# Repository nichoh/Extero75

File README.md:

# Extero75
keyboard

75% keyboard with 10 more extra keys and a knob on the left hand side. Will use USB C and have Backlight LED.

Progress:
Schematic is currently getting checked while doing some routing.

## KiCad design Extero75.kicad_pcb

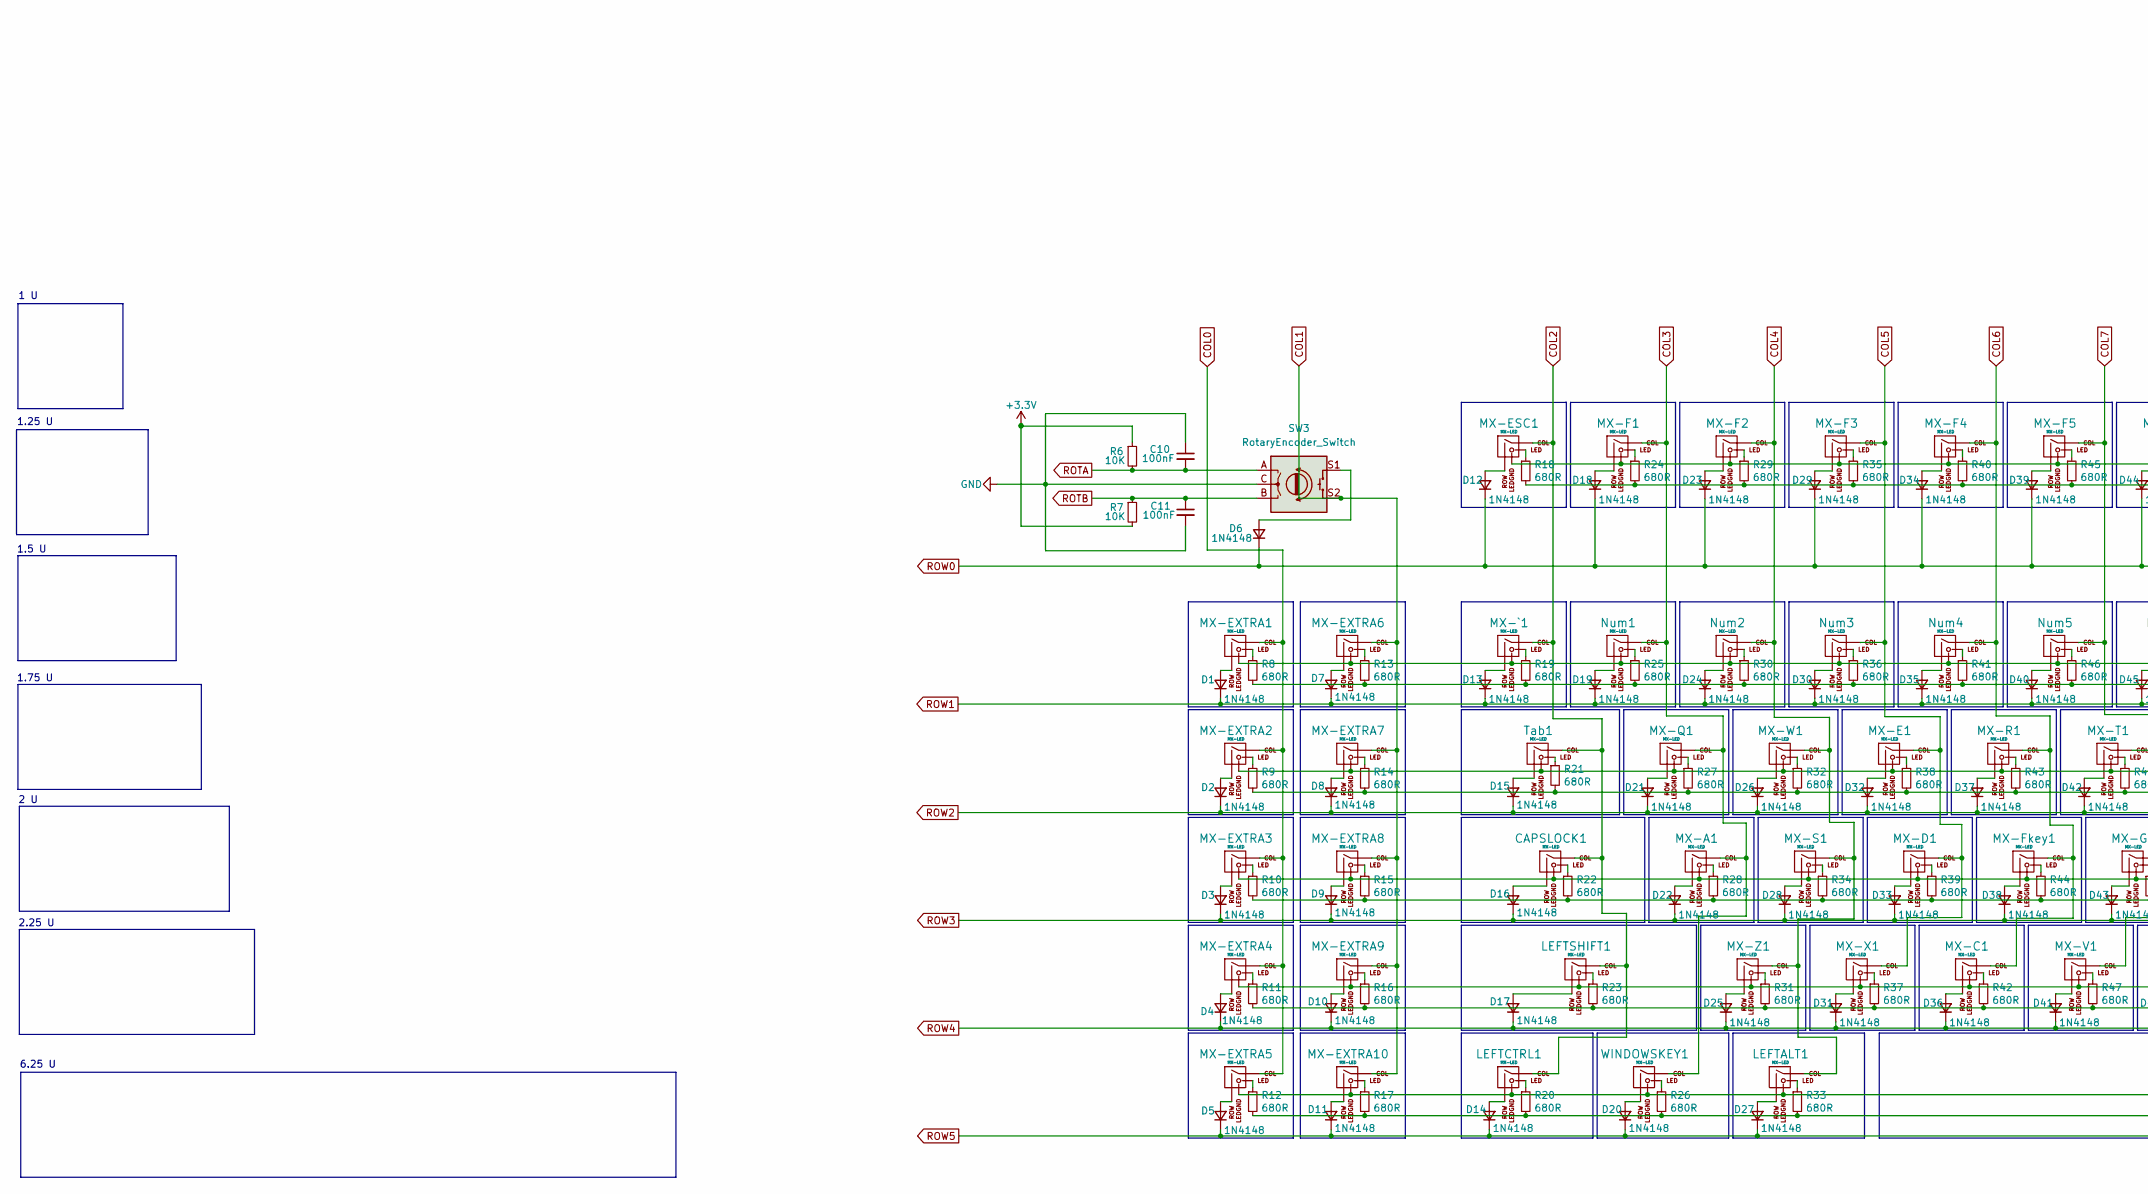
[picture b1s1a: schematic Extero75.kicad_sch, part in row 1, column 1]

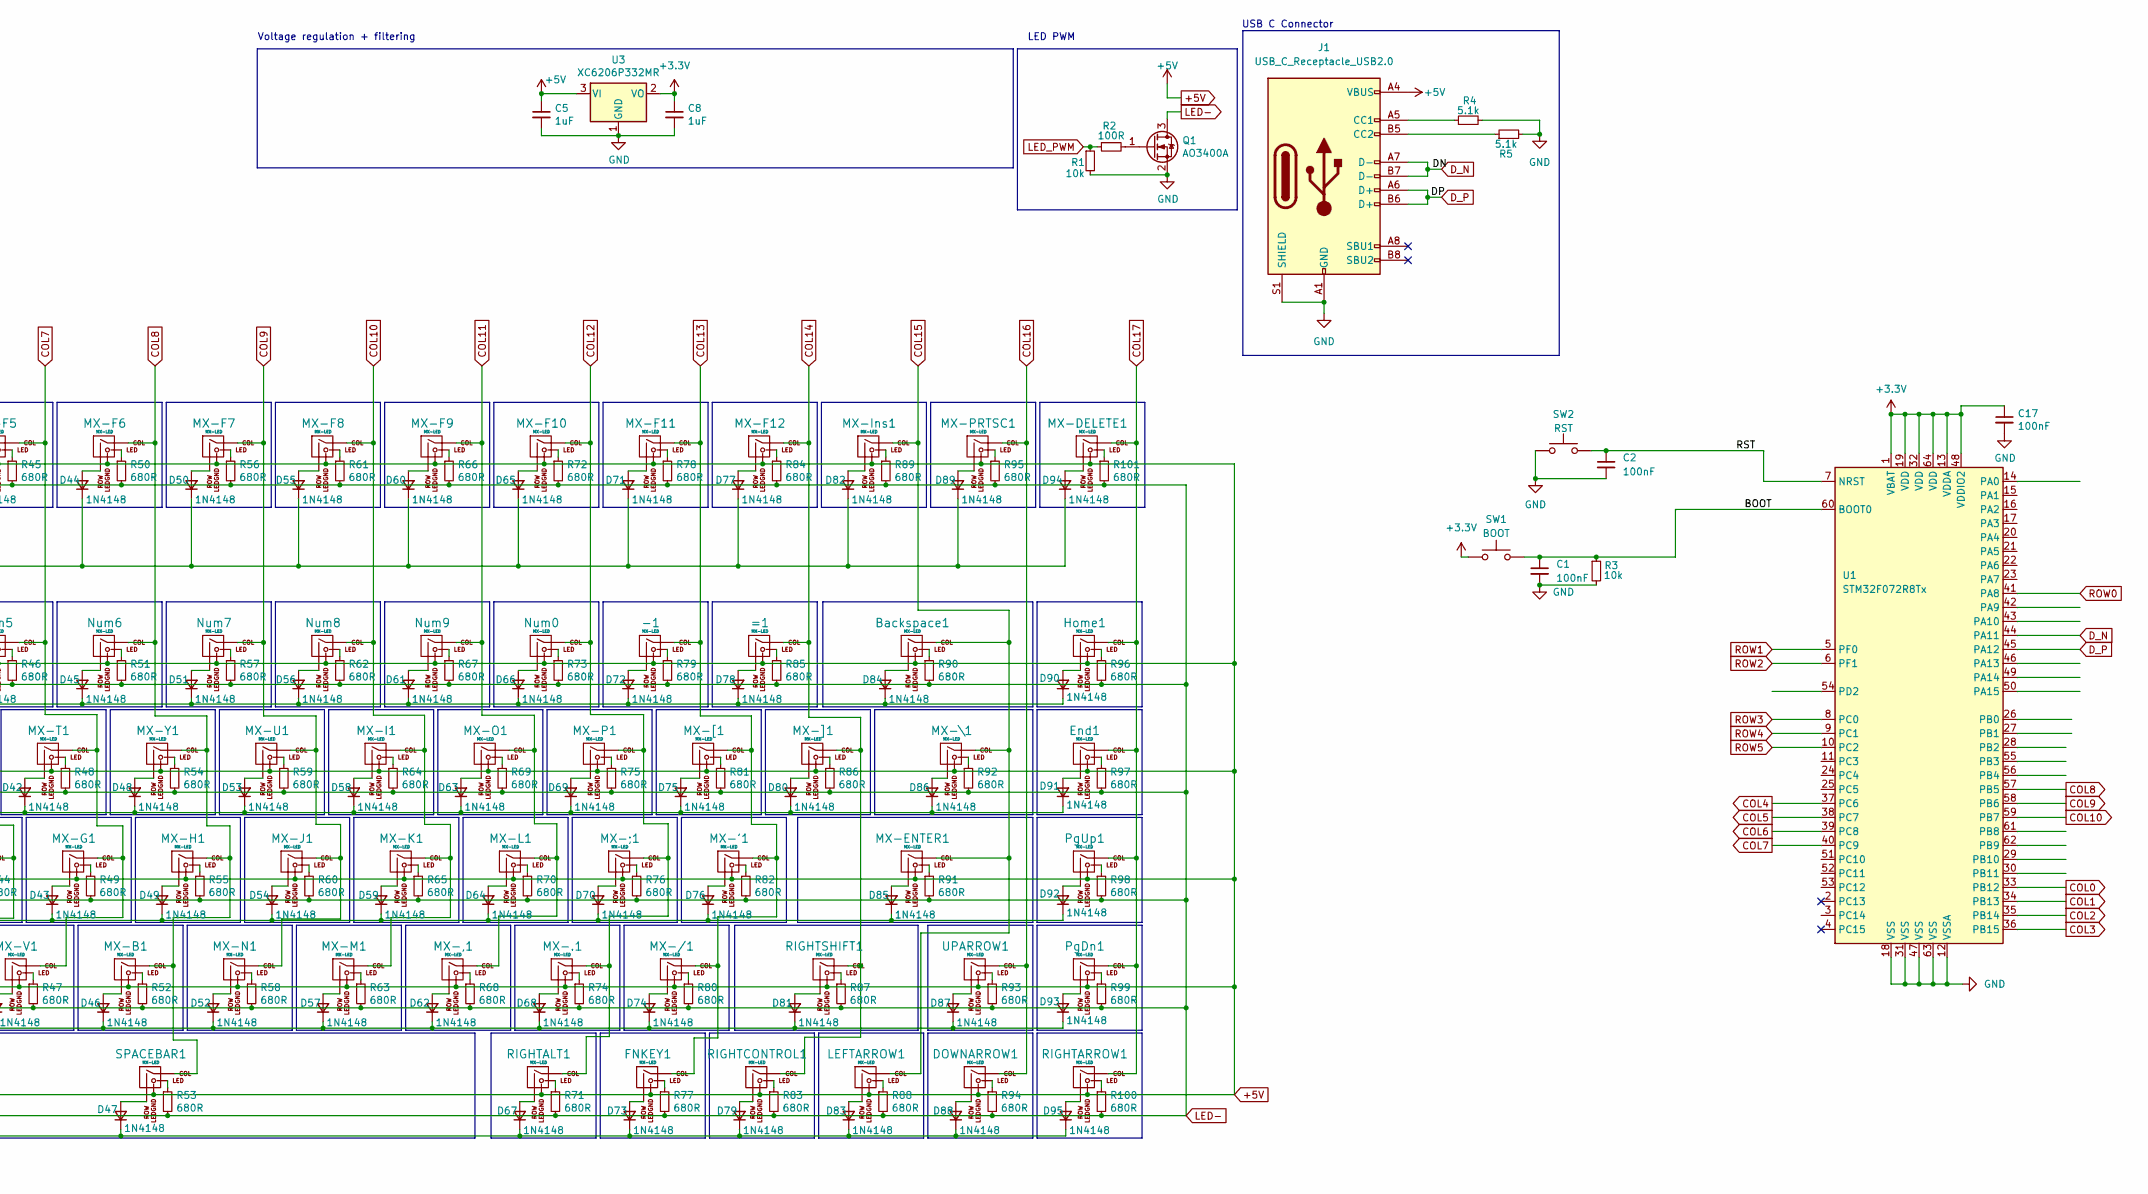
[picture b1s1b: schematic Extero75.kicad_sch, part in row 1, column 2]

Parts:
-1: MX-LED; MXOnly-1U-Hotswap-LED
=1: MX-LED; MXOnly-1U-Hotswap-LED
Backspace1: MX-LED; MXOnly-2U-Hotswap-LED
C1, C2, C10, C11: 100nF; C_0402_1005Metric
C5, C8: 1uF; C_0402_1005Metric; LCSC C52923
C17: 100nF; C_0402_1005Metric; LCSC C1525
CAPSLOCK1: MX-LED; MXOnly-1.75U-Hotswap-LED
D1, D2, D3, D4, D5, D6, D7, D8, D9, D10, D11, D12, D13, D14, D15, D16, D17, D18, D19, D20, D21, D22, D23, D24, D25, D26, D27, D28, D29, D30, D31, D32, D33, D34, D35, D36, D37, D38, D39, D40, D41, D42, D43, D44, D45, D46, D47, D48, D49, D50, D51, D52, D53, D54, D55, D56, D57, D58, D59, D60, D61, D62, D63, D64, D65, D66, D67, D68, D69, D70, D71, D72, D73, D74, D75, D76, D77, D78, D79, D80, D81, D82, D83, D84, D85, D86, D87, D88, D89, D90, D91, D92, D93, D94, D95: 1N4148; D_SOD-323F
DOWNARROW1: MX-LED; MXOnly-1U-Hotswap-LED
End1: MX-LED; MXOnly-1U-Hotswap-LED
FNKEY1: MX-LED; MXOnly-1U-Hotswap-LED
Home1: MX-LED; MXOnly-1U-Hotswap-LED
J1: USB_C_Receptacle_USB2.0; USB_C_Receptacle_GCT_USB4085
LEFTALT1: MX-LED; MXOnly-1.25U-Hotswap-LED
LEFTARROW1: MX-LED; MXOnly-1U-Hotswap-LED
LEFTCTRL1: MX-LED; MXOnly-1.25U-Hotswap-LED
LEFTSHIFT1: MX-LED; MXOnly-2.25U-Hotswap-LED
MX-'1: MX-LED; MXOnly-1U-Hotswap-LED
MX-,1: MX-LED; MXOnly-1U-Hotswap-LED
MX-.1: MX-LED; MXOnly-1U-Hotswap-LED
MX-/1: MX-LED; MXOnly-1U-Hotswap-LED
MX-;1: MX-LED; MXOnly-1U-Hotswap-LED
MX-A1: MX-LED; MXOnly-1U-Hotswap-LED
MX-B1: MX-LED; MXOnly-1U-Hotswap-LED
MX-C1: MX-LED; MXOnly-1U-Hotswap-LED
MX-D1: MX-LED; MXOnly-1U-Hotswap-LED
MX-DELETE1: MX-LED; MXOnly-1U-Hotswap-LED
MX-E1: MX-LED; MXOnly-1U-Hotswap-LED
MX-ENTER1: MX-LED; MXOnly-2.25U-Hotswap-LED
MX-ESC1: MX-LED; MXOnly-1U-Hotswap-LED
MX-EXTRA1, MX-EXTRA2, MX-EXTRA3, MX-EXTRA4, MX-EXTRA5, MX-EXTRA6, MX-EXTRA7, MX-EXTRA8, MX-EXTRA9, MX-EXTRA10: MX-LED; MXOnly-1U-Hotswap-LED
MX-F1, MX-F2, MX-F3, MX-F4, MX-F5, MX-F6, MX-F7, MX-F8, MX-F9, MX-F10, MX-F11, MX-F12: MX-LED; MXOnly-1U-Hotswap-LED
MX-Fkey1: MX-LED; MXOnly-1U-Hotswap-LED
MX-G1: MX-LED; MXOnly-1U-Hotswap-LED
MX-H1: MX-LED; MXOnly-1U-Hotswap-LED
MX-I1: MX-LED; MXOnly-1U-Hotswap-LED
MX-Ins1: MX-LED; MXOnly-1U-Hotswap-LED
MX-J1: MX-LED; MXOnly-1U-Hotswap-LED
MX-K1: MX-LED; MXOnly-1U-Hotswap-LED
MX-L1: MX-LED; MXOnly-1U-Hotswap-LED
MX-M1: MX-LED; MXOnly-1U-Hotswap-LED
MX-N1: MX-LED; MXOnly-1U-Hotswap-LED
MX-O1: MX-LED; MXOnly-1U-Hotswap-LED
MX-P1: MX-LED; MXOnly-1U-Hotswap-LED
MX-PRTSC1: MX-LED; MXOnly-1U-Hotswap-LED
MX-Q1: MX-LED; MXOnly-1U-Hotswap-LED
MX-R1: MX-LED; MXOnly-1U-Hotswap-LED
MX-S1: MX-LED; MXOnly-1U-Hotswap-LED
MX-T1: MX-LED; MXOnly-1U-Hotswap-LED
MX-U1: MX-LED; MXOnly-1U-Hotswap-LED
MX-V1: MX-LED; MXOnly-1U-Hotswap-LED
MX-W1: MX-LED; MXOnly-1U-Hotswap-LED
MX-X1: MX-LED; MXOnly-1U-Hotswap-LED
MX-Y1: MX-LED; MXOnly-1U-Hotswap-LED
MX-Z1: MX-LED; MXOnly-1U-Hotswap-LED
MX-[1: MX-LED; MXOnly-1U-Hotswap-LED
MX-\1: MX-LED; MXOnly-1.5U-Hotswap-LED
MX-]1: MX-LED; MXOnly-1U-Hotswap-LED
MX-`1: MX-LED; MXOnly-1U-Hotswap-LED
Num0, Num1, Num2, Num3, Num4, Num5, Num6, Num7, Num8, Num9: MX-LED; MXOnly-1U-Hotswap-LED
PgDn1: MX-LED; MXOnly-1U-Hotswap-LED
PgUp1: MX-LED; MXOnly-1U-Hotswap-LED
Q1: AO3400A; SOT-23; LCSC C20917
R1: 10k; R_0402_1005Metric; LCSC C25744
R2: 100R; R_0402_1005Metric; LCSC C25076
R3: 10k; R_0402_1005Metric
R4, R5: 5.1k; R_0603_1608Metric
R6, R7: 10K; R_0402_1005Metric
R8, R9, R10, R11, R12, R13, R14, R15, R16, R17, R18, R19, R20, R21, R22, R23, R24, R25, R26, R27, R28, R29, R30, R31, R32, R33, R34, R35, R36, R37, R38, R39, R40, R41, R42, R43, R44, R45, R46, R47, R48, R49, R50, R51, R52, R53, R54, R55, R56, R57, R58, R59, R60, R61, R62, R63, R64, R65, R66, R67, R68, R69, R70, R71, R72, R73, R74, R75, R76, R77, R78, R79, R80, R81, R82, R83, R84, R85, R86, R87, R88, R89, R90, R91, R92, R93, R94, R95, R96, R97, R98, R99, R100, R101: 680R; R_0603_1608Metric; LCSC C23228
RIGHTALT1: MX-LED; MXOnly-1U-Hotswap-LED
RIGHTARROW1: MX-LED; MXOnly-1U-Hotswap-LED
RIGHTCONTROL1: MX-LED; MXOnly-1U-Hotswap-LED
RIGHTSHIFT1: MX-LED; MXOnly-1.75U-Hotswap-LED
SPACEBAR1: MX-LED; MXOnly-6.25U-Hotswap-LED
SW1: BOOT; SW_SPST_SKQG_WithStem
SW2: RST; SW_SPST_SKQG_WithStem
SW3: RotaryEncoder_Switch; RotaryEncoder_Alps_EC11E-Switch_Vertical_H20mm
Tab1: MX-LED; MXOnly-1.5U-Hotswap-LED
U1: STM32F072R8Tx; LQFP-64_10x10mm_P0.5mm
U3: XC6206P332MR; SOT-23; LCSC C5446
UPARROW1: MX-LED; MXOnly-1U-Hotswap-LED
WINDOWSKEY1: MX-LED; MXOnly-1.25U-Hotswap-LED

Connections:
+3.3V: C8.1, C17.1, R6.1, R7.2, SW1.1, U1.1 (VBAT), U1.13 (VDDA), U1.19 (VDD), U1.32 (VDD), U1.48 (VDDIO2), U1.64 (VDD), U3.2 (VO)
+5V: -1.4 (LEDGND), =1.4 (LEDGND), Backspace1.4 (LEDGND), C5.1, CAPSLOCK1.4 (LEDGND), DOWNARROW1.4 (LEDGND), End1.4 (LEDGND), FNKEY1.4 (LEDGND), Home1.4 (LEDGND), J1.A4 (VBUS), J1.A9 (VBUS), J1.B4 (VBUS), J1.B9 (VBUS), LEFTALT1.4 (LEDGND), LEFTARROW1.4 (LEDGND), LEFTCTRL1.4 (LEDGND), LEFTSHIFT1.4 (LEDGND), MX-'1.4 (LEDGND), MX-,1.4 (LEDGND), MX-.1.4 (LEDGND), MX-/1.4 (LEDGND), MX-;1.4 (LEDGND), MX-A1.4 (LEDGND), MX-B1.4 (LEDGND), MX-C1.4 (LEDGND), MX-D1.4 (LEDGND), MX-DELETE1.4 (LEDGND), MX-E1.4 (LEDGND), MX-ENTER1.4 (LEDGND), MX-ESC1.4 (LEDGND), MX-EXTRA1.4 (LEDGND), MX-EXTRA2.4 (LEDGND), MX-EXTRA3.4 (LEDGND), MX-EXTRA4.4 (LEDGND), MX-EXTRA5.4 (LEDGND), MX-EXTRA6.4 (LEDGND), MX-EXTRA7.4 (LEDGND), MX-EXTRA8.4 (LEDGND), MX-EXTRA9.4 (LEDGND), MX-EXTRA10.4 (LEDGND), MX-F1.4 (LEDGND), MX-F2.4 (LEDGND), MX-F3.4 (LEDGND), MX-F4.4 (LEDGND), MX-F5.4 (LEDGND), MX-F6.4 (LEDGND), MX-F7.4 (LEDGND), MX-F8.4 (LEDGND), MX-F9.4 (LEDGND), MX-F10.4 (LEDGND), MX-F11.4 (LEDGND), MX-F12.4 (LEDGND), MX-Fkey1.4 (LEDGND), MX-G1.4 (LEDGND), MX-H1.4 (LEDGND), MX-I1.4 (LEDGND), MX-Ins1.4 (LEDGND), MX-J1.4 (LEDGND), MX-K1.4 (LEDGND), MX-L1.4 (LEDGND), MX-M1.4 (LEDGND), MX-N1.4 (LEDGND), MX-O1.4 (LEDGND), MX-P1.4 (LEDGND), MX-PRTSC1.4 (LEDGND), MX-Q1.4 (LEDGND), MX-R1.4 (LEDGND), MX-S1.4 (LEDGND), MX-T1.4 (LEDGND), MX-U1.4 (LEDGND), MX-V1.4 (LEDGND), MX-W1.4 (LEDGND), MX-X1.4 (LEDGND), MX-Y1.4 (LEDGND), MX-Z1.4 (LEDGND), MX-[1.4 (LEDGND), MX-\1.4 (LEDGND), MX-]1.4 (LEDGND), MX-`1.4 (LEDGND), Num0.4 (LEDGND), Num1.4 (LEDGND), Num2.4 (LEDGND), Num3.4 (LEDGND), Num4.4 (LEDGND), Num5.4 (LEDGND), Num6.4 (LEDGND), Num7.4 (LEDGND), Num8.4 (LEDGND), Num9.4 (LEDGND), PgDn1.4 (LEDGND), PgUp1.4 (LEDGND), RIGHTALT1.4 (LEDGND), RIGHTARROW1.4 (LEDGND), RIGHTCONTROL1.4 (LEDGND), RIGHTSHIFT1.4 (LEDGND), SPACEBAR1.4 (LEDGND), Tab1.4 (LEDGND), U3.3 (VI), UPARROW1.4 (LEDGND), WINDOWSKEY1.4 (LEDGND)
/BOOT: C1.1, R3.1, SW1.2, U1.60 (BOOT0)
/RST: C2.1, SW2.2, U1.7 (NRST)
COL0: MX-EXTRA1.1 (COL), MX-EXTRA2.1 (COL), MX-EXTRA3.1 (COL), MX-EXTRA4.1 (COL), MX-EXTRA5.1 (COL), U1.33 (PB12)
COL1: MX-EXTRA6.1 (COL), MX-EXTRA7.1 (COL), MX-EXTRA8.1 (COL), MX-EXTRA9.1 (COL), MX-EXTRA10.1 (COL), SW3.S2, U1.34 (PB13)
COL2: CAPSLOCK1.1 (COL), LEFTCTRL1.1 (COL), LEFTSHIFT1.1 (COL), MX-ESC1.1 (COL), MX-`1.1 (COL), Tab1.1 (COL), U1.35 (PB14)
COL3: MX-A1.1 (COL), MX-F1.1 (COL), MX-Q1.1 (COL), Num1.1 (COL), U1.36 (PB15), WINDOWSKEY1.1 (COL)
COL4: LEFTALT1.1 (COL), MX-F2.1 (COL), MX-S1.1 (COL), MX-W1.1 (COL), MX-Z1.1 (COL), Num2.1 (COL), U1.37 (PC6)
COL5: MX-D1.1 (COL), MX-E1.1 (COL), MX-F3.1 (COL), MX-X1.1 (COL), Num3.1 (COL), U1.38 (PC7)
COL6: MX-C1.1 (COL), MX-F4.1 (COL), MX-Fkey1.1 (COL), MX-R1.1 (COL), Num4.1 (COL), U1.39 (PC8)
COL7: MX-F5.1 (COL), MX-G1.1 (COL), MX-T1.1 (COL), MX-V1.1 (COL), Num5.1 (COL), U1.40 (PC9)
COL8: MX-B1.1 (COL), MX-F6.1 (COL), MX-H1.1 (COL), MX-Y1.1 (COL), Num6.1 (COL), SPACEBAR1.1 (COL), U1.57 (PB5)
COL9: MX-F7.1 (COL), MX-J1.1 (COL), MX-N1.1 (COL), MX-U1.1 (COL), Num7.1 (COL), U1.58 (PB6)
COL10: MX-F8.1 (COL), MX-I1.1 (COL), MX-K1.1 (COL), MX-M1.1 (COL), Num8.1 (COL), U1.59 (PB7)
COL11: MX-,1.1 (COL), MX-F9.1 (COL), MX-L1.1 (COL), MX-O1.1 (COL), Num9.1 (COL)
COL12: MX-.1.1 (COL), MX-;1.1 (COL), MX-F10.1 (COL), MX-P1.1 (COL), Num0.1 (COL), RIGHTALT1.1 (COL)
COL13: -1.1 (COL), FNKEY1.1 (COL), MX-'1.1 (COL), MX-/1.1 (COL), MX-F11.1 (COL), MX-[1.1 (COL)
COL14: =1.1 (COL), MX-F12.1 (COL), MX-]1.1 (COL), RIGHTCONTROL1.1 (COL), RIGHTSHIFT1.1 (COL)
COL15: Backspace1.1 (COL), LEFTARROW1.1 (COL), MX-ENTER1.1 (COL), MX-Ins1.1 (COL), MX-\1.1 (COL)
COL16: DOWNARROW1.1 (COL), MX-PRTSC1.1 (COL), UPARROW1.1 (COL)
COL17: End1.1 (COL), Home1.1 (COL), MX-DELETE1.1 (COL), PgDn1.1 (COL), PgUp1.1 (COL), RIGHTARROW1.1 (COL)
D_N: J1.A7 (D-), J1.B7 (D-), U1.44 (PA11)
D_P: J1.A6 (D+), J1.B6 (D+), U1.45 (PA12)
GND: C1.2, C2.2, C5.2, C8.2, C10.1, C11.2, C17.2, J1.A1 (GND), J1.A12 (GND), J1.B1 (GND), J1.B12 (GND), J1.S1 (SHIELD), Q1.2 (S), R1.2, R3.2, R4.2, R5.2, SW2.1, SW3.C, U1.12 (VSSA), U1.18 (VSS), U1.31 (VSS), U1.47 (VSS), U1.63 (VSS), U3.1 (GND)
LED-: Q1.3 (D), R8.2, R9.2, R10.2, R11.2, R12.2, R13.2, R14.2, R15.2, R16.2, R17.2, R18.2, R19.2, R20.2, R21.2, R22.2, R23.2, R24.2, R25.2, R26.2, R27.2, R28.2, R29.2, R30.2, R31.2, R32.2, R33.2, R34.2, R35.2, R36.2, R37.2, R38.2, R39.2, R40.2, R41.2, R42.2, R43.2, R44.2, R45.2, R46.2, R47.2, R48.2, R49.2, R50.2, R51.2, R52.2, R53.2, R54.2, R55.2, R56.2, R57.2, R58.2, R59.2, R60.2, R61.2, R62.2, R63.2, R64.2, R65.2, R66.2, R67.2, R68.2, R69.2, R70.2, R71.2, R72.2, R73.2, R74.2, R75.2, R76.2, R77.2, R78.2, R79.2, R80.2, R81.2, R82.2, R83.2, R84.2, R85.2, R86.2, R87.2, R88.2, R89.2, R90.2, R91.2, R92.2, R93.2, R94.2, R95.2, R96.2, R97.2, R98.2, R99.2, R100.2, R101.2
LED_PWM: R1.1, R2.1
unnamed: -1.2 (ROW), D72.2 (A)
unnamed: -1.3 (LED), R79.1
unnamed: =1.2 (ROW), D78.2 (A)
unnamed: =1.3 (LED), R85.1
unnamed: Backspace1.2 (ROW), D84.2 (A)
unnamed: Backspace1.3 (LED), R90.1
unnamed: CAPSLOCK1.2 (ROW), D16.2 (A)
unnamed: CAPSLOCK1.3 (LED), R22.1
unnamed: D1.2 (A), MX-EXTRA1.2 (ROW)
unnamed: D2.2 (A), MX-EXTRA2.2 (ROW)
unnamed: D3.2 (A), MX-EXTRA3.2 (ROW)
unnamed: D4.2 (A), MX-EXTRA4.2 (ROW)
unnamed: D5.2 (A), MX-EXTRA5.2 (ROW)
unnamed: D6.2 (A), SW3.S1
unnamed: D7.2 (A), MX-EXTRA6.2 (ROW)
unnamed: D8.2 (A), MX-EXTRA7.2 (ROW)
unnamed: D9.2 (A), MX-EXTRA8.2 (ROW)
unnamed: D10.2 (A), MX-EXTRA9.2 (ROW)
unnamed: D11.2 (A), MX-EXTRA10.2 (ROW)
unnamed: D12.2 (A), MX-ESC1.2 (ROW)
unnamed: D13.2 (A), MX-`1.2 (ROW)
unnamed: D14.2 (A), LEFTCTRL1.2 (ROW)
unnamed: D15.2 (A), Tab1.2 (ROW)
unnamed: D17.2 (A), LEFTSHIFT1.2 (ROW)
unnamed: D18.2 (A), MX-F1.2 (ROW)
unnamed: D19.2 (A), Num1.2 (ROW)
unnamed: D20.2 (A), WINDOWSKEY1.2 (ROW)
unnamed: D21.2 (A), MX-Q1.2 (ROW)
unnamed: D22.2 (A), MX-A1.2 (ROW)
unnamed: D23.2 (A), MX-F2.2 (ROW)
unnamed: D24.2 (A), Num2.2 (ROW)
unnamed: D25.2 (A), MX-Z1.2 (ROW)
unnamed: D26.2 (A), MX-W1.2 (ROW)
unnamed: D27.2 (A), LEFTALT1.2 (ROW)
unnamed: D28.2 (A), MX-S1.2 (ROW)
unnamed: D29.2 (A), MX-F3.2 (ROW)
unnamed: D30.2 (A), Num3.2 (ROW)
unnamed: D31.2 (A), MX-X1.2 (ROW)
unnamed: D32.2 (A), MX-E1.2 (ROW)
unnamed: D33.2 (A), MX-D1.2 (ROW)
unnamed: D34.2 (A), MX-F4.2 (ROW)
unnamed: D35.2 (A), Num4.2 (ROW)
unnamed: D36.2 (A), MX-C1.2 (ROW)
unnamed: D37.2 (A), MX-R1.2 (ROW)
unnamed: D38.2 (A), MX-Fkey1.2 (ROW)
unnamed: D39.2 (A), MX-F5.2 (ROW)
unnamed: D40.2 (A), Num5.2 (ROW)
unnamed: D41.2 (A), MX-V1.2 (ROW)
unnamed: D42.2 (A), MX-T1.2 (ROW)
unnamed: D43.2 (A), MX-G1.2 (ROW)
unnamed: D44.2 (A), MX-F6.2 (ROW)
unnamed: D45.2 (A), Num6.2 (ROW)
unnamed: D46.2 (A), MX-B1.2 (ROW)
unnamed: D47.2 (A), SPACEBAR1.2 (ROW)
unnamed: D48.2 (A), MX-Y1.2 (ROW)
unnamed: D49.2 (A), MX-H1.2 (ROW)
unnamed: D50.2 (A), MX-F7.2 (ROW)
unnamed: D51.2 (A), Num7.2 (ROW)
unnamed: D52.2 (A), MX-N1.2 (ROW)
unnamed: D53.2 (A), MX-U1.2 (ROW)
unnamed: D54.2 (A), MX-J1.2 (ROW)
unnamed: D55.2 (A), MX-F8.2 (ROW)
unnamed: D56.2 (A), Num8.2 (ROW)
unnamed: D57.2 (A), MX-M1.2 (ROW)
unnamed: D58.2 (A), MX-I1.2 (ROW)
unnamed: D59.2 (A), MX-K1.2 (ROW)
unnamed: D60.2 (A), MX-F9.2 (ROW)
unnamed: D61.2 (A), Num9.2 (ROW)
unnamed: D62.2 (A), MX-,1.2 (ROW)
unnamed: D63.2 (A), MX-O1.2 (ROW)
unnamed: D64.2 (A), MX-L1.2 (ROW)
unnamed: D65.2 (A), MX-F10.2 (ROW)
unnamed: D66.2 (A), Num0.2 (ROW)
unnamed: D67.2 (A), RIGHTALT1.2 (ROW)
unnamed: D68.2 (A), MX-.1.2 (ROW)
unnamed: D69.2 (A), MX-P1.2 (ROW)
unnamed: D70.2 (A), MX-;1.2 (ROW)
unnamed: D71.2 (A), MX-F11.2 (ROW)
unnamed: D73.2 (A), FNKEY1.2 (ROW)
unnamed: D74.2 (A), MX-/1.2 (ROW)
unnamed: D75.2 (A), MX-[1.2 (ROW)
unnamed: D76.2 (A), MX-'1.2 (ROW)
unnamed: D77.2 (A), MX-F12.2 (ROW)
unnamed: D79.2 (A), RIGHTCONTROL1.2 (ROW)
unnamed: D80.2 (A), MX-]1.2 (ROW)
unnamed: D81.2 (A), RIGHTSHIFT1.2 (ROW)
unnamed: D82.2 (A), MX-Ins1.2 (ROW)
unnamed: D83.2 (A), LEFTARROW1.2 (ROW)
unnamed: D85.2 (A), MX-ENTER1.2 (ROW)
unnamed: D86.2 (A), MX-\1.2 (ROW)
unnamed: D87.2 (A), UPARROW1.2 (ROW)
unnamed: D88.2 (A), DOWNARROW1.2 (ROW)
unnamed: D89.2 (A), MX-PRTSC1.2 (ROW)
unnamed: D90.2 (A), Home1.2 (ROW)
unnamed: D91.2 (A), End1.2 (ROW)
unnamed: D92.2 (A), PgUp1.2 (ROW)
unnamed: D93.2 (A), PgDn1.2 (ROW)
unnamed: D94.2 (A), MX-DELETE1.2 (ROW)
unnamed: D95.2 (A), RIGHTARROW1.2 (ROW)
unnamed: DOWNARROW1.3 (LED), R94.1
unnamed: End1.3 (LED), R97.1
unnamed: FNKEY1.3 (LED), R77.1
unnamed: Home1.3 (LED), R96.1
unnamed: J1.A5 (CC1), R4.1
unnamed: J1.B5 (CC2), R5.1
unnamed: LEFTALT1.3 (LED), R33.1
unnamed: LEFTARROW1.3 (LED), R88.1
unnamed: LEFTCTRL1.3 (LED), R20.1
unnamed: LEFTSHIFT1.3 (LED), R23.1
unnamed: MX-'1.3 (LED), R82.1
unnamed: MX-,1.3 (LED), R68.1
unnamed: MX-.1.3 (LED), R74.1
unnamed: MX-/1.3 (LED), R80.1
unnamed: MX-;1.3 (LED), R76.1
unnamed: MX-A1.3 (LED), R28.1
unnamed: MX-B1.3 (LED), R52.1
unnamed: MX-C1.3 (LED), R42.1
unnamed: MX-D1.3 (LED), R39.1
unnamed: MX-DELETE1.3 (LED), R101.1
unnamed: MX-E1.3 (LED), R38.1
unnamed: MX-ENTER1.3 (LED), R91.1
unnamed: MX-ESC1.3 (LED), R18.1
unnamed: MX-EXTRA1.3 (LED), R8.1
unnamed: MX-EXTRA2.3 (LED), R9.1
unnamed: MX-EXTRA3.3 (LED), R10.1
unnamed: MX-EXTRA4.3 (LED), R11.1
unnamed: MX-EXTRA5.3 (LED), R12.1
unnamed: MX-EXTRA6.3 (LED), R13.1
unnamed: MX-EXTRA7.3 (LED), R14.1
unnamed: MX-EXTRA8.3 (LED), R15.1
unnamed: MX-EXTRA9.3 (LED), R16.1
unnamed: MX-EXTRA10.3 (LED), R17.1
unnamed: MX-F1.3 (LED), R24.1
unnamed: MX-F2.3 (LED), R29.1
unnamed: MX-F3.3 (LED), R35.1
unnamed: MX-F4.3 (LED), R40.1
unnamed: MX-F5.3 (LED), R45.1
unnamed: MX-F6.3 (LED), R50.1
unnamed: MX-F7.3 (LED), R56.1
unnamed: MX-F8.3 (LED), R61.1
unnamed: MX-F9.3 (LED), R66.1
unnamed: MX-F10.3 (LED), R72.1
unnamed: MX-F11.3 (LED), R78.1
unnamed: MX-F12.3 (LED), R84.1
unnamed: MX-Fkey1.3 (LED), R44.1
unnamed: MX-G1.3 (LED), R49.1
unnamed: MX-H1.3 (LED), R55.1
unnamed: MX-I1.3 (LED), R64.1
unnamed: MX-Ins1.3 (LED), R89.1
unnamed: MX-J1.3 (LED), R60.1
unnamed: MX-K1.3 (LED), R65.1
unnamed: MX-L1.3 (LED), R70.1
unnamed: MX-M1.3 (LED), R63.1
unnamed: MX-N1.3 (LED), R58.1
unnamed: MX-O1.3 (LED), R69.1
unnamed: MX-P1.3 (LED), R75.1
unnamed: MX-PRTSC1.3 (LED), R95.1
unnamed: MX-Q1.3 (LED), R27.1
unnamed: MX-R1.3 (LED), R43.1
unnamed: MX-S1.3 (LED), R34.1
unnamed: MX-T1.3 (LED), R48.1
unnamed: MX-U1.3 (LED), R59.1
unnamed: MX-V1.3 (LED), R47.1
unnamed: MX-W1.3 (LED), R32.1
unnamed: MX-X1.3 (LED), R37.1
unnamed: MX-Y1.3 (LED), R54.1
unnamed: MX-Z1.3 (LED), R31.1
unnamed: MX-[1.3 (LED), R81.1
unnamed: MX-\1.3 (LED), R92.1
unnamed: MX-]1.3 (LED), R86.1
unnamed: MX-`1.3 (LED), R19.1
unnamed: Num0.3 (LED), R73.1
unnamed: Num1.3 (LED), R25.1
unnamed: Num2.3 (LED), R30.1
unnamed: Num3.3 (LED), R36.1
unnamed: Num4.3 (LED), R41.1
unnamed: Num5.3 (LED), R46.1
unnamed: Num6.3 (LED), R51.1
unnamed: Num7.3 (LED), R57.1
unnamed: Num8.3 (LED), R62.1
unnamed: Num9.3 (LED), R67.1
unnamed: PgDn1.3 (LED), R99.1
unnamed: PgUp1.3 (LED), R98.1
unnamed: Q1.1 (G), R2.2
unnamed: R21.1, Tab1.3 (LED)
unnamed: R26.1, WINDOWSKEY1.3 (LED)
unnamed: R53.1, SPACEBAR1.3 (LED)
unnamed: R71.1, RIGHTALT1.3 (LED)
unnamed: R83.1, RIGHTCONTROL1.3 (LED)
unnamed: R87.1, RIGHTSHIFT1.3 (LED)
unnamed: R93.1, UPARROW1.3 (LED)
unnamed: R100.1, RIGHTARROW1.3 (LED)
ROTA: C10.2, R6.2, SW3.A
ROTB: C11.1, R7.1, SW3.B
ROW0: D6.1 (K), D12.1 (K), D18.1 (K), D23.1 (K), D29.1 (K), D34.1 (K), D39.1 (K), D44.1 (K), D50.1 (K), D55.1 (K), D60.1 (K), D65.1 (K), D71.1 (K), D77.1 (K), D82.1 (K), D89.1 (K), D94.1 (K), U1.41 (PA8)
ROW1: D1.1 (K), D7.1 (K), D13.1 (K), D19.1 (K), D24.1 (K), D30.1 (K), D35.1 (K), D40.1 (K), D45.1 (K), D51.1 (K), D56.1 (K), D61.1 (K), D66.1 (K), D72.1 (K), D78.1 (K), D84.1 (K), D90.1 (K), U1.5 (PF0)
ROW2: D2.1 (K), D8.1 (K), D15.1 (K), D21.1 (K), D26.1 (K), D32.1 (K), D37.1 (K), D42.1 (K), D48.1 (K), D53.1 (K), D58.1 (K), D63.1 (K), D69.1 (K), D75.1 (K), D80.1 (K), D86.1 (K), D91.1 (K), U1.6 (PF1)
ROW3: D3.1 (K), D9.1 (K), D16.1 (K), D22.1 (K), D28.1 (K), D33.1 (K), D38.1 (K), D43.1 (K), D49.1 (K), D54.1 (K), D59.1 (K), D64.1 (K), D70.1 (K), D76.1 (K), D85.1 (K), D92.1 (K), U1.8 (PC0)
ROW4: D4.1 (K), D10.1 (K), D17.1 (K), D25.1 (K), D31.1 (K), D36.1 (K), D41.1 (K), D46.1 (K), D52.1 (K), D57.1 (K), D62.1 (K), D68.1 (K), D74.1 (K), D81.1 (K), D87.1 (K), D93.1 (K), U1.9 (PC1)
ROW5: D5.1 (K), D11.1 (K), D14.1 (K), D20.1 (K), D27.1 (K), D47.1 (K), D67.1 (K), D73.1 (K), D79.1 (K), D83.1 (K), D88.1 (K), D95.1 (K), U1.10 (PC2)

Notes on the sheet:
1 U
LED PWM
6.25 U
1.25 U
2.25 U
1.5 U
1.75 U
Voltage regulation + filtering
2 U
USB C Connector

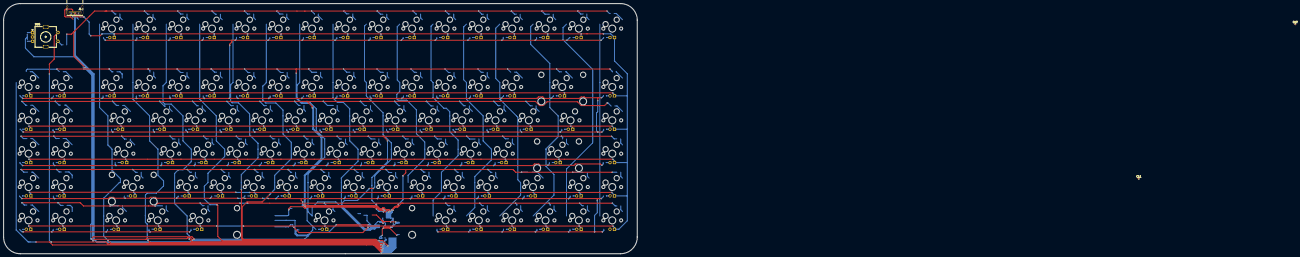
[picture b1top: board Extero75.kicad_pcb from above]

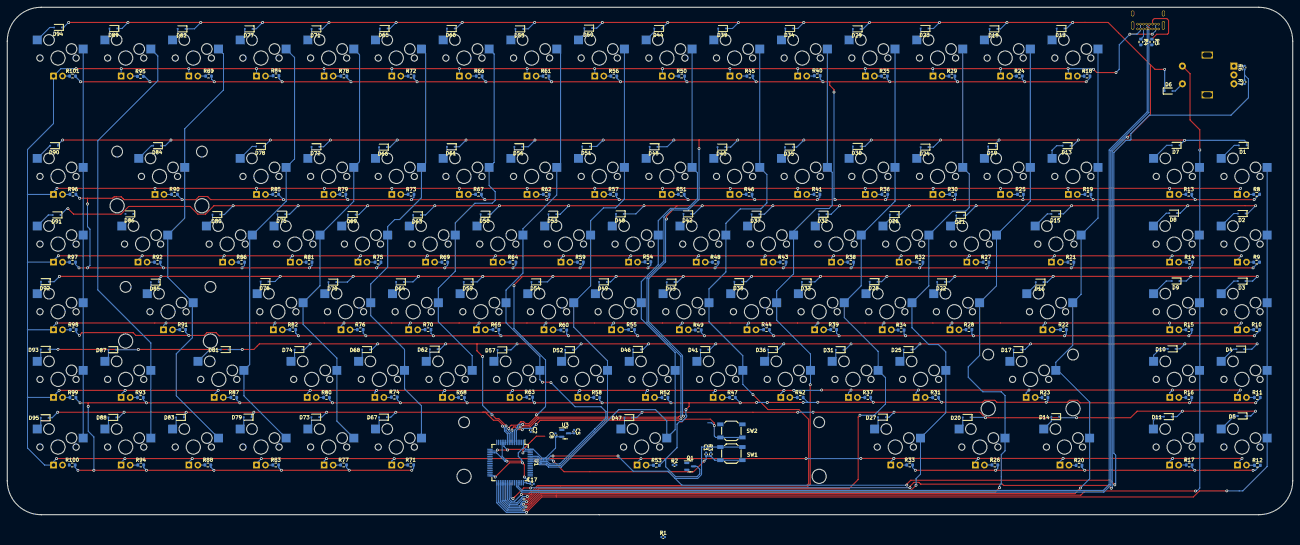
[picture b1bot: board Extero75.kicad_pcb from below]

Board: 2 copper layers, 362.0 x 142.9 mm, 304 parts (206 on the bottom side), 227 nets.

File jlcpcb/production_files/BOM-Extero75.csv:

Comment,Designator,Footprint,LCSC
100nF,"C1,C10,C11,C14,C2,C3,C4,C6,C7,C9",C_0603_1608Metric,C14663
1uf,"C12,C5,C8",C_0603_1608Metric,C15849
USB_C_Receptacle_USB2.0,J1,USB_C_Receptacle_GCT_USB4105-xx-A_16P_TopMnt_Horizontal,C165948
10uf,C13,C_0603_1608Metric,C19702
5.1k,"R4,R5",R_0603_1608Metric,C23186
10k,"R3,R6,R7",R_0603_1608Metric,C25804
BOOT,"SW1,SW2",SW_SPST_SKQG_WithStem,C318884
RotaryEncoder_Switch,SW3,RotaryEncoder_Alps_EC11E-Switch_Vertical_H20mm,C361165
MX-LED,"A1,B1,Backspace1,CAPSLOCK1,Ckey1,CloseBracket1,CommaSign1,DELETE1,DOWNARROW1,Dkey1,DotSign1,E1,ENTER1,ESC1,EXTRA1,EXTRA10,EXTRA2,EXTRA3,EXTRA4,EXTRA5,EXTRA6,EXTRA7,EXTRA8,EXTRA9,End1,EqualSign1,F1,F10,F11,F12,F2,F3,F4,F5,F6,F7,F8,F9,FNKEY1,Fkey1,G1,Hkey1,Home1,I1,Ins1,Jkey1,K1,L1,LEFTALT1,LEFTARROW1,LEFTCTRL1,LEFTSHIFT1,M1,Matilda1,MinusSign1,N1,Num0,Num1,Num2,Num3,Num4,Num5,Num6,Num7,Num8,Num9,O1,OpenBracket1,P1,PRTSC1,PgDn1,PgUp1,Q1,QuestionMark1,Quote1,R1,RIGHTALT1,RIGHTARROW1,RIGHTCONTROL1,RIGHTSHIFT1,S1,SPACEBAR1,Semicolon1,Slash1,T1,Tab1,U2,UPARROW1,V1,W1,WINDOWSKEY1,X1,Y1,Z1",MXOnly-1U-Hotswap,C5156480
XC6206P332MR,U3,SOT-23,C5446
1N4148,"D1,D10,D11,D12,D13,D14,D15,D16,D17,D18,D19,D2,D20,D21,D22,D23,D24,D25,D26,D27,D28,D29,D3,D30,D31,D32,D33,D34,D35,D36,D37,D38,D39,D4,D40,D41,D42,D43,D44,D45,D46,D47,D48,D49,D5,D50,D51,D52,D53,D54,D55,D56,D57,D58,D59,D6,D60,D61,D62,D63,D64,D65,D66,D67,D68,D69,D7,D70,D71,D72,D73,D74,D75,D76,D77,D78,D79,D8,D80,D81,D82,D83,D84,D85,D86,D87,D88,D89,D9,D90,D91,D92,D93,D94,D95",D_SOD-123,C81598
STM32F072R8Tx,U1,LQFP-64_10x10mm_P0.5mm,C87900
MountingHole,H3,MountingHole_2.2mm_M2,
MountingHole,H2,MountingHole_2.2mm_M2,
MountingHole,H4,MountingHole_2.2mm_M2,
MountingHole,H1,MountingHole_2.2mm_M2,

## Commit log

2023-02-15 change name
2023-02-17 some more routing
2023-02-17 Fix decoupling capacitor schematic for Voltage regulator + Some more routing
2023-02-23 Rerouting + Plate + Top Case
2023-03-01 Removing LED's
2023-03-01 Changing footprints
2023-07-27 Keycaps
    Test Keycaps for 3d print testing
